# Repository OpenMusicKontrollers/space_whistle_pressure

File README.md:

# Space Whistle Pressure Sensor

## About
This is the PCB design for the respiratory air pressure sensor for the [Space Whistle](http://hackaday.io/project/2011-Space-Whistle) - an expressive open wind controller.

## Prerequisites
To be used with [KiCAD](http://www.kicad-pcb.org).

## License
This is open source hardware and licensed under [CERN OHL v.1.2](http://ohwr.org/cernohl).

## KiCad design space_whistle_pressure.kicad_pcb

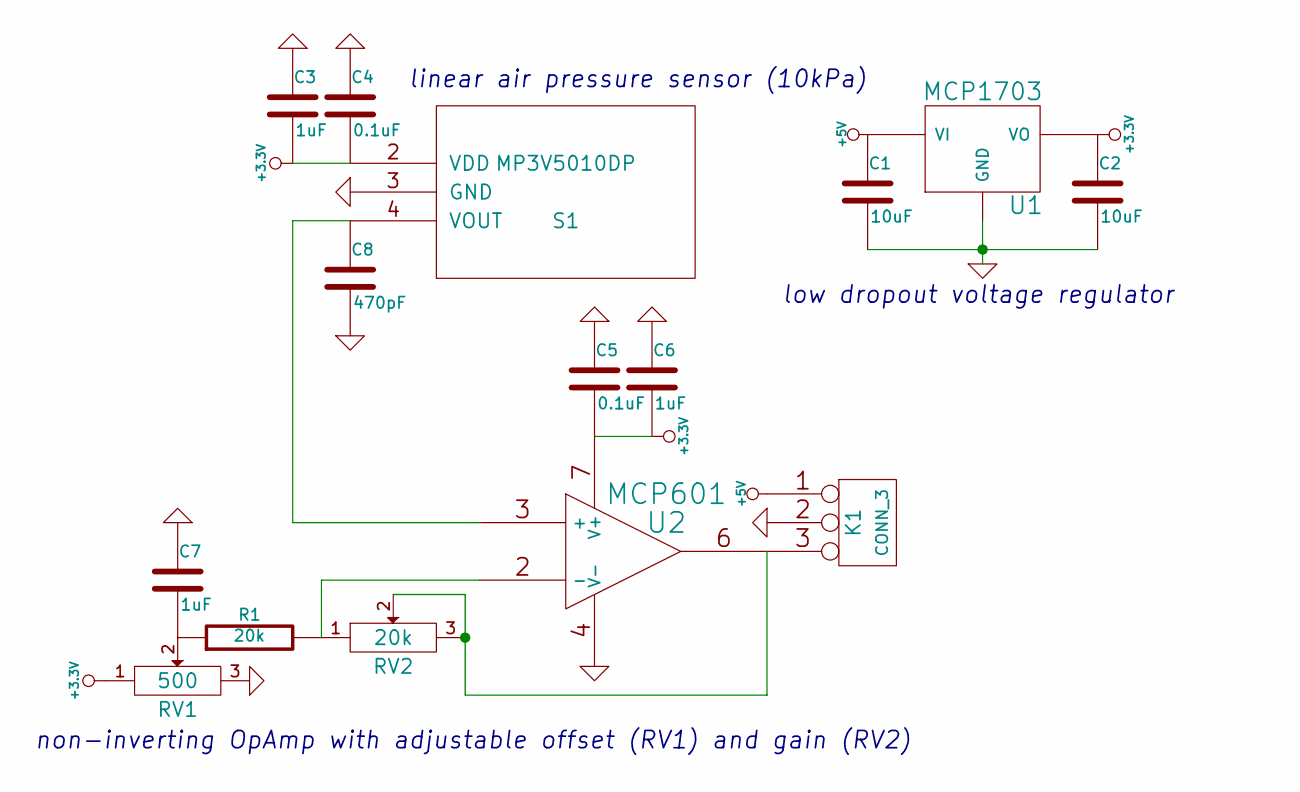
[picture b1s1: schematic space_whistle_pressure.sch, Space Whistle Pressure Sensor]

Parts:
C1, C2: 10uF
C3, C6, C7: 1uF
C4, C5: 0.1uF
C8: 470pF
K1: CONN_3
R1: 20k
RV1: 500
RV2: 20k
S1: MP3V5010DP; MODULE
U1: MCP1703
U2: MCP601

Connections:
+3.3V: C2.1, C3.2, C4.2, C5.2, C6.2, RV1.1, S1.2 (VDD), U1.2 (VO), U2.7 (V+)
+5V: C1.1, K1.1, U1.1 (VI)
GND: C1.2, C2.2, C3.1, C4.1, C5.1, C6.1, C7.1, C8.2, K1.2 (PM), RV1.3, S1.3 (GND), U1.3 (GND), U2.4 (V-)
unnamed: C7.2, R1.1, RV1.2
unnamed: C8.1, S1.4 (VOUT), U2.3 (+)
unnamed: K1.3, RV2.2, RV2.3, U2.6
unnamed: R1.2, RV2.1, U2.2 (-)

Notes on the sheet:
linear air pressure sensor (10kPa)
low dropout voltage regulator
non-inverting OpAmp with adjustable offset (RV1) and gain (RV2)

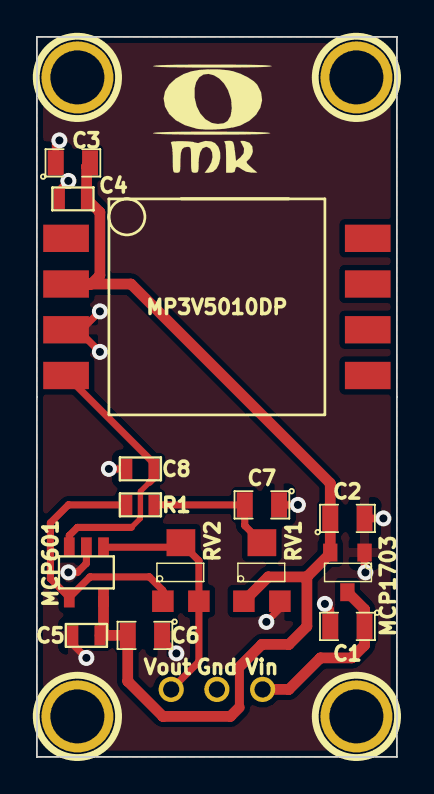
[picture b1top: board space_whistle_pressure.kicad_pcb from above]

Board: 2 copper layers, 20.0 x 40.0 mm, 19 parts (0 on the bottom side), 7 nets.

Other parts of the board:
1PIN, 1PIN#2, 1PIN#3, 1PIN#4: P***; 1pin

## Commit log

2014-07-30 paste dims
2014-07-30 set origin
2014-08-04 add Digi-Key part numbers

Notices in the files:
space_whistle_pressure.kicad_pcb:
Released under CERN OHL v.1.2
Copyright (c) 2014 Hanspeter Portner (dev@open-music-kontrollers.ch)
